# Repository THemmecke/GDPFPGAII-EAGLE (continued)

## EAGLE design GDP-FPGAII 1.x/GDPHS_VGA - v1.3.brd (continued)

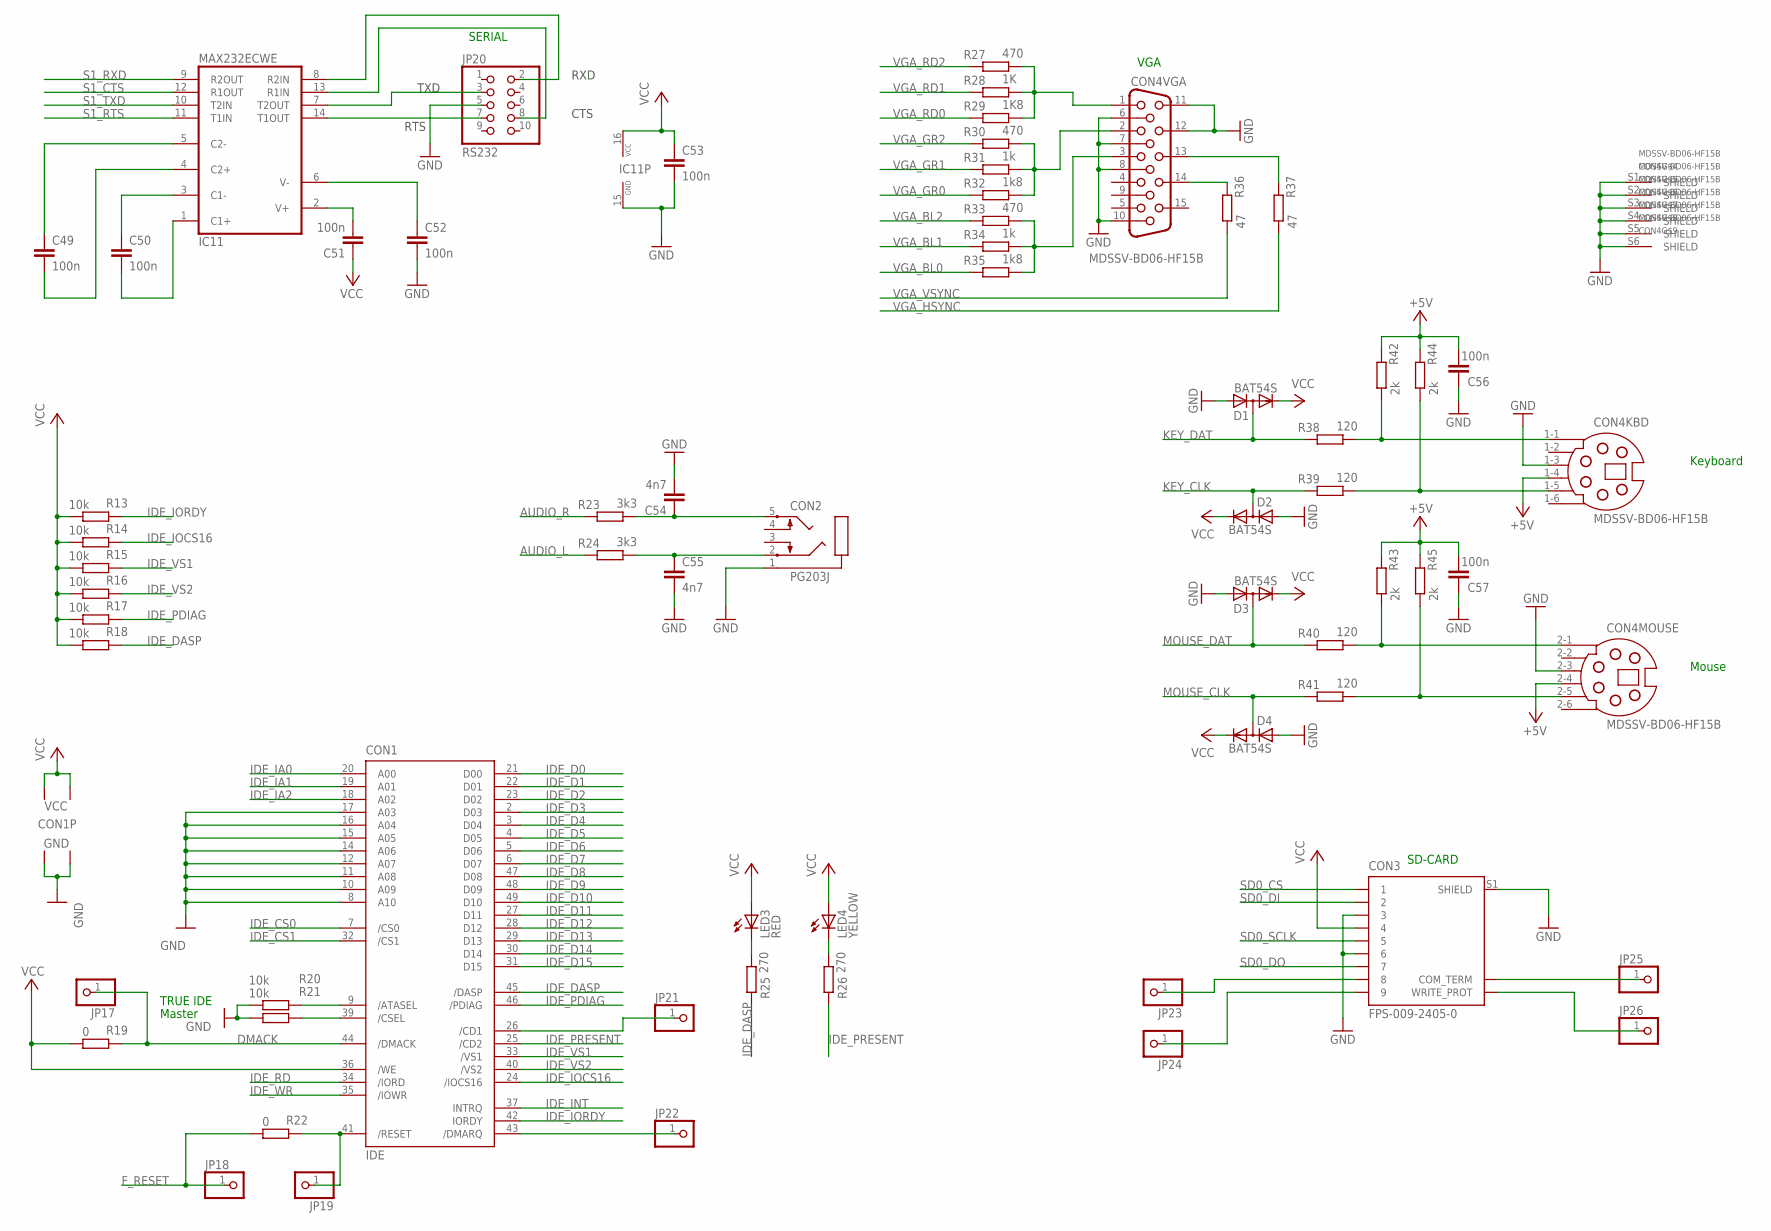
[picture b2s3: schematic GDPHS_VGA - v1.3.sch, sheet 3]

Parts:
C49, C50, C51, C52, C53, C56, C57: 100n; C0805
C54, C55: 4n7; C0805
CON1: IDE; CF-050-P2-X03-10-DS-1; MPN CF-050P2-103-10-DS1
CON2: PG203J
CON3: FPS-009-2405-0; MPN FPS-009-2405-0
CON4: MDSSV-BD06-HF15B; MDSSV-BD06-HF15-B; MPN 999-H15-PS2L571
D1, D2, D3, D4: BAT54S; SOT23
IC11: MAX232ECWE; SO16L
JP17, JP18, JP19, JP21, JP22, JP23, JP24, JP25, JP26: PINHD-1X1; 1X01
JP20: RS232; 2X05
LED3: RED; CHIPLED_0805
LED4: YELLOW; CHIPLED_0805
R13, R14, R15, R16, R17, R18, R20, R21: 10k; M0805
R19, R22: 0; M0805
R23, R24: 3k3; M0805
R25, R26: 270; M0805
R27, R30, R33: 470; M0805
R28: 1K; M0805
R29: 1K8; M0805
R31, R34: 1k; M0805
R32, R35: 1k8; M0805
R36, R37: 47; M0805
R38, R39, R40, R41: 120; M0805
R42, R43, R44, R45: 2k; M0805

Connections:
+5V: C56.2, C57.2, CON4.1-4 (4), CON4.2-4 (4), R42.1, R43.1, R44.1, R45.1; also elsewhere on the board
AUDIO_L: R24.1; also elsewhere on the board
AUDIO_R: R23.1; also elsewhere on the board
DMACK: CON1.44 (/DMACK), JP17.1, R19.1
F_RESET: JP18.1, R22.2; also elsewhere on the board
GND: C52.2, C53.2, C54.2, C55.2, C56.1, C57.1, CON1.1 (GND1), CON1.8 (A10), CON1.10 (A09), CON1.11 (A08), CON1.12 (A07), CON1.14 (A06), CON1.15 (A05), CON1.16 (A04), CON1.17 (A03), CON1.50 (GND2), CON2.1, CON3.3, CON3.6, CON3.S1 (SHIELD), CON4.1-3 (3), CON4.2-3 (3), CON4.6, CON4.7, CON4.8, CON4.10, CON4.11, CON4.12, CON4.S1 (SHIELD), CON4.S2 (SHIELD), CON4.S3 (SHIELD), CON4.S4 (SHIELD), CON4.S5 (SHIELD), CON4.S6 (SHIELD), D1.1 (A), D2.1 (A), D3.1 (A), D4.1 (A), IC11.15 (GND), JP20.5, R20.2, R21.2; also elsewhere on the board
IDE_CS0: CON1.7 (/CS0); also elsewhere on the board
IDE_CS1: CON1.32 (/CS1); also elsewhere on the board
IDE_D0: CON1.21 (D00); also elsewhere on the board
IDE_D1: CON1.22 (D01); also elsewhere on the board
IDE_D2: CON1.23 (D02); also elsewhere on the board
IDE_D3: CON1.2 (D03); also elsewhere on the board
IDE_D4: CON1.3 (D04); also elsewhere on the board
IDE_D5: CON1.4 (D05); also elsewhere on the board
IDE_D6: CON1.5 (D06); also elsewhere on the board
IDE_D7: CON1.6 (D07); also elsewhere on the board
IDE_D8: CON1.47 (D08); also elsewhere on the board
IDE_D9: CON1.48 (D09); also elsewhere on the board
IDE_D10: CON1.49 (D10); also elsewhere on the board
IDE_D11: CON1.27 (D11); also elsewhere on the board
IDE_D12: CON1.28 (D12); also elsewhere on the board
IDE_D13: CON1.29 (D13); also elsewhere on the board
IDE_D14: CON1.30 (D14); also elsewhere on the board
IDE_D15: CON1.31 (D15); also elsewhere on the board
IDE_DASP: CON1.45 (/DASP), R18.1, R25.1
IDE_IA0: CON1.20 (A00); also elsewhere on the board
IDE_IA1: CON1.19 (A01); also elsewhere on the board
IDE_IA2: CON1.18 (A02); also elsewhere on the board
IDE_INT: CON1.37 (INTRQ); also elsewhere on the board
IDE_IOCS16: CON1.24 (/IOCS16), R14.1
IDE_IORDY: CON1.42 (IORDY), R13.1
IDE_PDIAG: CON1.46 (/PDIAG), R17.1
IDE_PRESENT: CON1.25 (/CD2), R26.1
IDE_RD: CON1.34 (/IORD); also elsewhere on the board
IDE_VS1: CON1.33 (/VS1), R15.1
IDE_VS2: CON1.40 (/VS2), R16.1
IDE_WR: CON1.35 (/IOWR); also elsewhere on the board
KEY_CLK: D2.3 (AC), R39.1; also elsewhere on the board
KEY_DAT: D1.3 (AC), R38.1; also elsewhere on the board
MOUSE_CLK: D4.3 (AC), R41.1; also elsewhere on the board
MOUSE_DAT: D3.3 (AC), R40.1; also elsewhere on the board
unnamed: C50.2, IC11.1 (C1+)
unnamed: LED3.C, R25.2
unnamed: C50.1, IC11.3 (C1-)
unnamed: C49.2, IC11.4 (C2+)
unnamed: C49.1, IC11.5 (C2-)
unnamed: C52.1, IC11.6 (V-)
unnamed: C51.2, IC11.2 (V+)
unnamed: LED4.C, R26.2
unnamed: IC11.8 (R2IN), JP20.2
unnamed: IC11.13 (R1IN), JP20.8
unnamed: IC11.7 (T2OUT), JP20.3
unnamed: CON4.1, R27.2, R28.2, R29.2
unnamed: CON4.2, R30.2, R31.2, R32.2
unnamed: CON4.3, R33.2, R34.2, R35.2
unnamed: CON4.13, R37.1
unnamed: CON4.14, R36.1
unnamed: CON4.1-1 (1), R38.2, R42.2
unnamed: CON4.1-5 (5), R39.2, R44.2
unnamed: CON4.2-1 (1), R40.2, R43.2
unnamed: CON4.2-5 (5), R41.2, R45.2
unnamed: CON1.39 (/CSEL), R21.1
unnamed: CON1.9 (/ATASEL), R20.1
unnamed: C54.1, CON2.5, R23.2
unnamed: C55.1, CON2.2, R24.2
unnamed: IC11.14 (T1OUT), JP20.7
unnamed: CON1.41 (/RESET), JP19.1, R22.1
unnamed: CON1.43 (/DMARQ), JP22.1
unnamed: CON1.26 (/CD1), JP21.1
unnamed: CON3.8, JP23.1
unnamed: CON3.9, JP24.1
unnamed: CON3.CD (COM_TERM), JP25.1
unnamed: CON3.WP (WRITE_PROT), JP26.1
S1_CTS: IC11.12 (R1OUT); also elsewhere on the board
S1_RTS: IC11.11 (T1IN); also elsewhere on the board
S1_RXD: IC11.9 (R2OUT); also elsewhere on the board
S1_TXD: IC11.10 (T2IN); also elsewhere on the board
SD0_CS: CON3.1; also elsewhere on the board
SD0_DI: CON3.2; also elsewhere on the board
SD0_DO: CON3.7; also elsewhere on the board
SD0_SCLK: CON3.5; also elsewhere on the board
VCC: C51.1, C53.1, CON1.13 (VCC2), CON1.36 (/WE), CON1.38 (VCC1), CON3.4, D1.2 (C), D2.2 (C), D3.2 (C), D4.2 (C), IC11.16 (VCC), LED3.A, LED4.A, R13.2, R14.2, R15.2, R16.2, R17.2, R18.2, R19.2; also elsewhere on the board
VGA_BL0: R35.1; also elsewhere on the board
VGA_BL1: R34.1; also elsewhere on the board
VGA_BL2: R33.1; also elsewhere on the board
VGA_GR0: R32.1; also elsewhere on the board
VGA_GR1: R31.1; also elsewhere on the board
VGA_GR2: R30.1; also elsewhere on the board
VGA_HSYNC: R37.2; also elsewhere on the board
VGA_RD0: R29.1; also elsewhere on the board
VGA_RD1: R28.1; also elsewhere on the board
VGA_RD2: R27.1; also elsewhere on the board
VGA_VSYNC: R36.2; also elsewhere on the board

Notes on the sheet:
SERIAL
SD-CARD
VGA
Keyboard
Mouse
Master
TRUE IDE
RXD
CTS
TXD
RTS

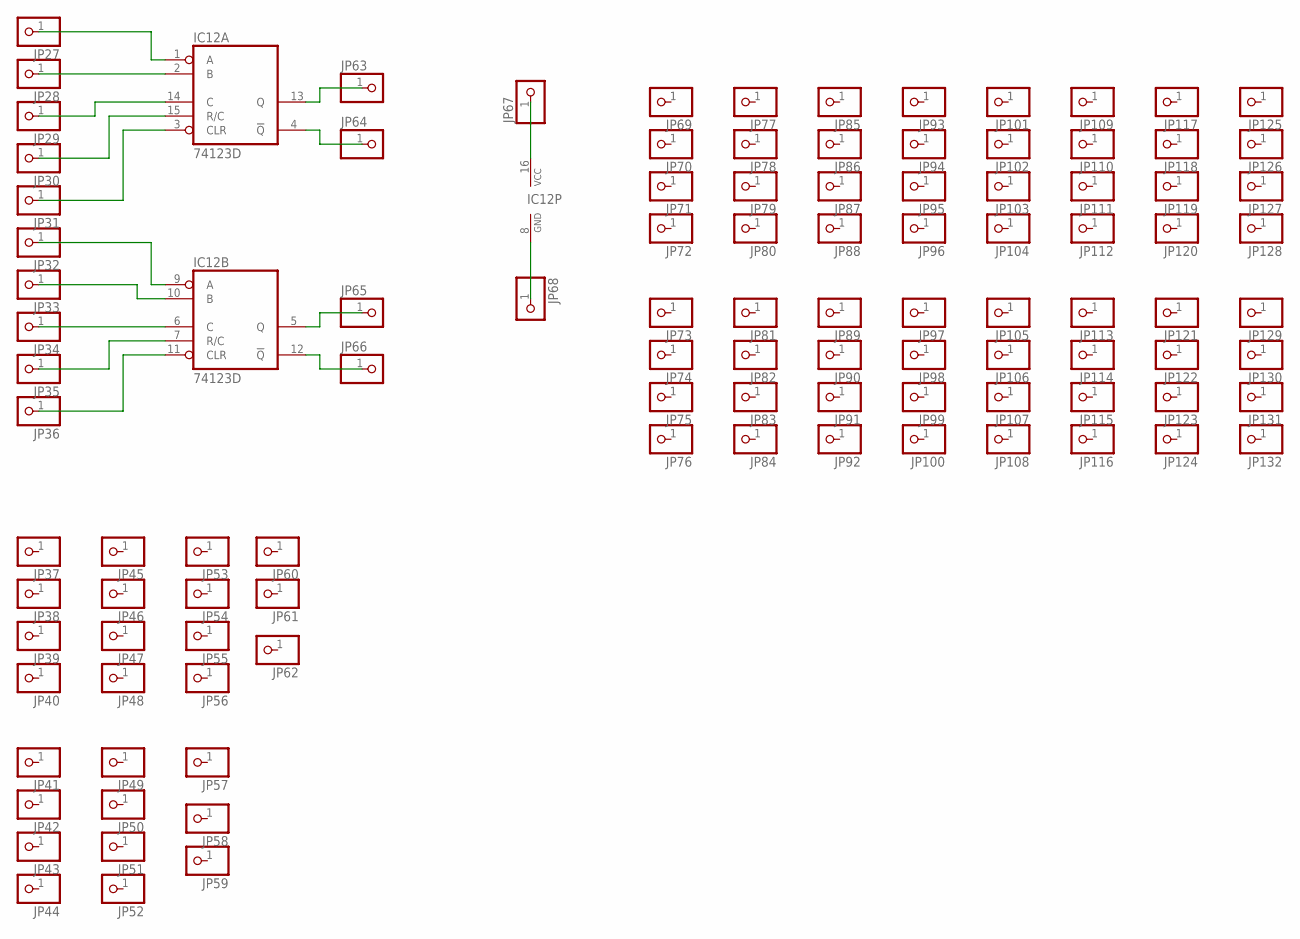
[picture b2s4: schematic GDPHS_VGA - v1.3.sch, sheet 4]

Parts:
IC12: 74123D; SO16
JP27, JP28, JP29, JP30, JP31, JP32, JP33, JP34, JP35, JP36, JP37, JP38, JP39, JP40, JP41, JP42, JP43, JP44, JP45, JP46, JP47, JP48, JP49, JP50, JP51, JP52, JP53, JP54, JP55, JP56, JP57, JP58, JP59, JP60, JP61, JP62, JP63, JP64, JP65, JP66, JP67, JP68, JP69, JP70, JP71, JP72, JP73, JP74, JP75, JP76, JP77, JP78, JP79, JP80, JP81, JP82, JP83, JP84, JP85, JP86, JP87, JP88, JP89, JP90, JP91, JP92, JP93, JP94, JP95, JP96, JP97, JP98, JP99, JP100, JP101, JP102, JP103, JP104, JP105, JP106, JP107, JP108, JP109, JP110, JP111, JP112, JP113, JP114, JP115, JP116, JP117, JP118, JP119, JP120, JP121, JP122, JP123, JP124, JP125, JP126, JP127, JP128, JP129, JP130, JP131, JP132: PINHD-1X1; 1X01

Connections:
unnamed: IC12.1 (A), JP27.1
unnamed: IC12.2 (B), JP28.1
unnamed: IC12.14 (C), JP29.1
unnamed: IC12.15 (R/C), JP30.1
unnamed: IC12.3 (CLR), JP31.1
unnamed: IC12.13 (Q), JP63.1
unnamed: IC12.4 (!Q), JP64.1
unnamed: IC12.9 (A), JP32.1
unnamed: IC12.10 (B), JP33.1
unnamed: IC12.6 (C), JP34.1
unnamed: IC12.16 (VCC), JP67.1
unnamed: IC12.8 (GND), JP68.1
unnamed: IC12.7 (R/C), JP35.1
unnamed: IC12.11 (CLR), JP36.1
unnamed: IC12.5 (Q), JP65.1
unnamed: IC12.12 (!Q), JP66.1

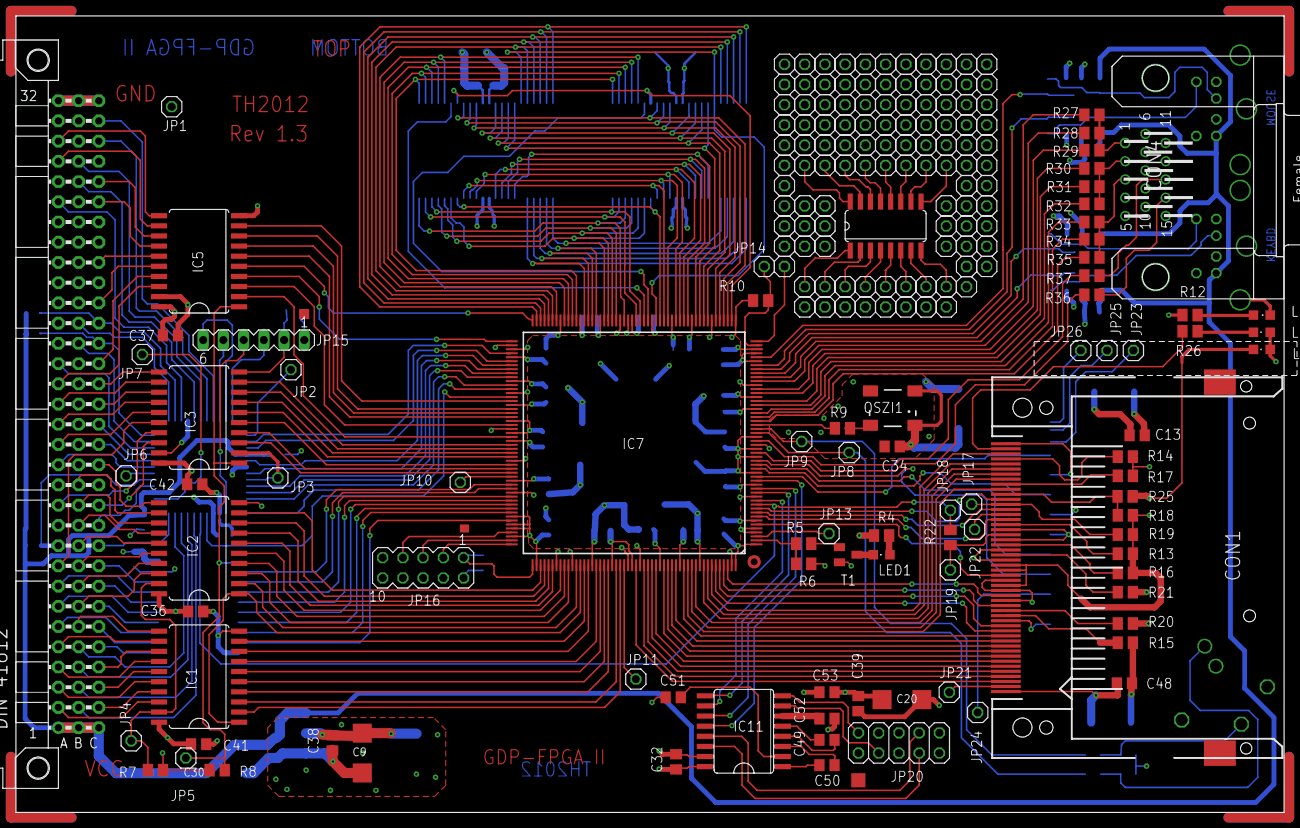
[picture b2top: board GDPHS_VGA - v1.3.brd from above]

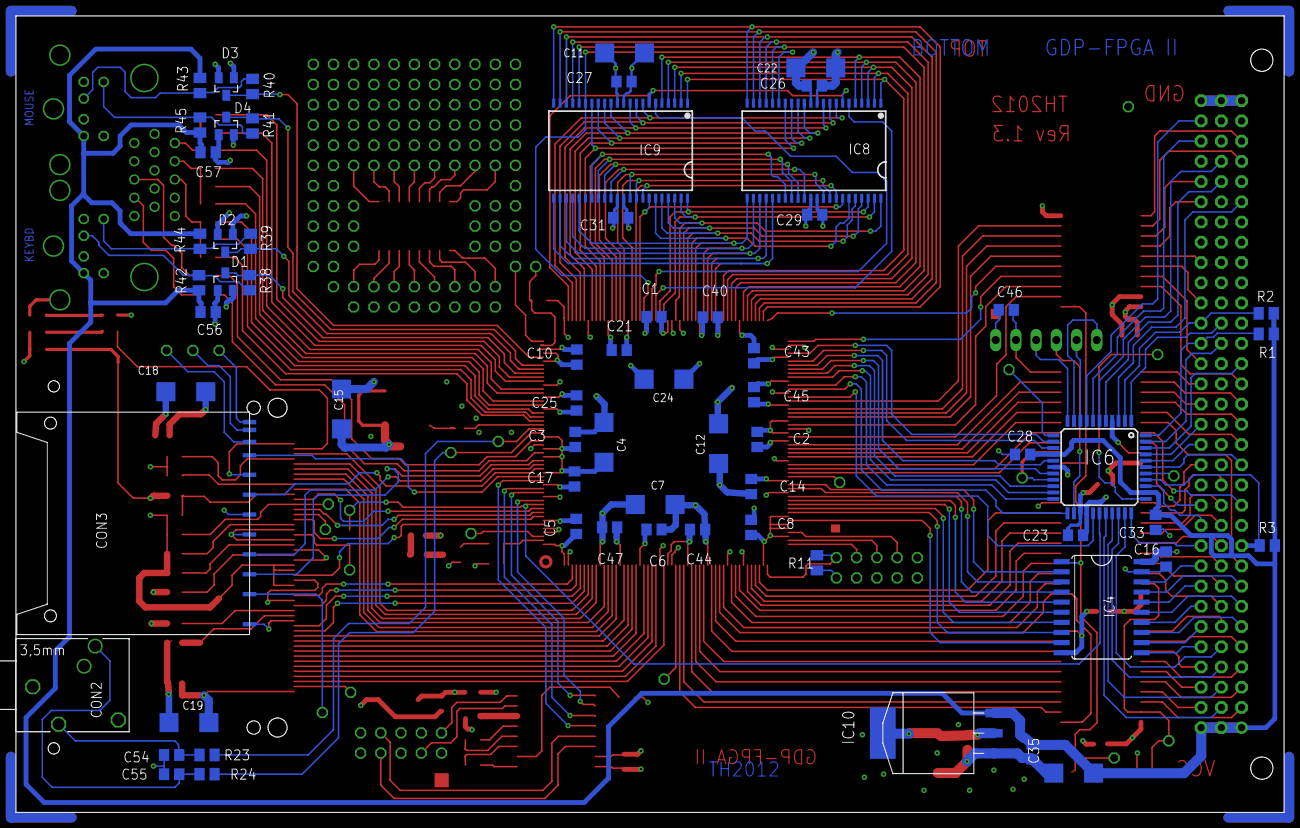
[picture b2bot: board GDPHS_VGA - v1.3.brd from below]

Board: 4 copper layers, 159.3 x 100.0 mm, 261 parts (65 on the bottom side), 284 nets.

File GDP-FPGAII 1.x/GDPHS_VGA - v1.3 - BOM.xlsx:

Qty | Value | Device | Package | Parts | Description | MF | MPN | DIGIKEY | FARNELL | REICHELT
4 | 0 | R-EU_M0805 | M0805 | R7, R8, R19, R22 | RESISTOR, European symbol |  |  |  |  | SMD-0805 [10,0K]
1 | 100 | R-EU_M0805 | M0805 | R10 | RESISTOR, European symbol |  |  |  |  | SMD-0805 [10,0K]
43 | 100n | C-EUC0805 | C0805 | C1, C2, C3, C5, C6, C8, C10, C13, C14, C16, C17, C21, C23, C25, C26, C27, C28, 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 | CAPACITOR, European symbol |  |  |  |  | X7R-G0805 [100N]
12 | 10k | R-EU_M0805 | M0805 | R1, R2, R3, R6, R13, R14, R15, R16, R17, R18, R20, R21 | RESISTOR, European symbol |  |  |  |  | SMD-0805 [10,0K]
12 | 10µ/16 | CPOL-EUSMCC | SMC_C | C4, C7, C9, C11, C12, C15, C18, C19, C20, C22, C24, C30 | POLARIZED CAPACITOR, European symbol |  |  |  |  | SMD TAN [10/16]
4 | 120 | R-EU_M0805 | M0805 | R38, R39, R40, R41 | RESISTOR, European symbol |  |  |  |  | SMD-0805 [10,0K]
1 | 1K | R-EU_M0805 | M0805 | R28 | RESISTOR, European symbol |  |  |  |  | SMD-0805 [10,0K]
1 | 1K8 | R-EU_M0805 | M0805 | R29 | RESISTOR, European symbol |  |  |  |  | SMD-0805 [10,0K]
2 | 1k | R-EU_M0805 | M0805 | R31, R34 | RESISTOR, European symbol |  |  |  |  | SMD-0805 [10,0K]
2 | 1k8 | R-EU_M0805 | M0805 | R32, R35 | RESISTOR, European symbol |  |  |  |  | SMD-0805 [10,0K]
1 | 220 | R-EU_M0805 | M0805 | R4 | RESISTOR, European symbol |  |  |  |  | SMD-0805 [10,0K]
3 | 270 | R-EU_M0805 | M0805 | R12, R25, R26 | RESISTOR, European symbol |  |  |  |  | SMD-0805 [10,0K]
4 | 2k | R-EU_M0805 | M0805 | R42, R43, R44, R45 | RESISTOR, European symbol |  |  |  |  | SMD-0805 [10,0K]
1 | 330 | R-EU_M0805 | M0805 | R9 | RESISTOR, European symbol |  |  |  |  | SMD-0805 [10,0K]
2 | 3k3 | R-EU_M0805 | M0805 | R23, R24 | RESISTOR, European symbol |  |  |  |  | SMD-0805 [10,0K]
2 | 47 | R-EU_M0805 | M0805 | R36, R37 | RESISTOR, European symbol |  |  |  |  | SMD-0805 [10,0K]
3 | 470 | R-EU_M0805 | M0805 | R27, R30, R33 | RESISTOR, European symbol |  |  |  |  | SMD-0805 [10,0K]
1 | 4k7 | R-EU_M0805 | M0805 | R11 | RESISTOR, European symbol |  |  |  |  | SMD-0805 [10,0K]
2 | 4n7 | C-EUC0805 | C0805 | C54, C55 | CAPACITOR, European symbol |  |  |  |  | X7R-G0805 [100N]
1 | 5k6 | R-EU_M0805 | M0805 | R5 | RESISTOR, European symbol |  |  |  |  | SMD-0805 [10,0K]
1 | 74123D | 74123D | SO16 | IC12 | Retriggerable monostable MULTIVIBRATOR
5 | 74LVC245 | 74HCT245DW | SO20W | IC1, IC2, IC3, IC4, IC5 | Octal BUS TRANSCEIVER, 3-state | Texas Instruments | SN74LVC245ADWR | 296-1232-1-ND
4 | BAT54S | DIODE_2CACA-SOT23 | SOT23 | D1, D2, D3, D4 | 2 Diodes - Cathode-Anode|Cathode-Anode |  |  |  |  | BAT 54S SMD
1 | BSS138 | BSS123 | SOT23 | T1 | N-CHANNEL MOS FET | Fairchild Semiconductor | BSS138 |  |  | BSS 138 SMD
1 | CFPS-39 40MHz | CRYSTAL_RESONATORCFPS7X | CFPS7X | OSZI1 | CRYSTAL RESONATOR | IQD FREQUENCY PRODUCTS | LF SPXO018042 - QUARZ, 40MHZ, 15PF, SMD |  | 9713565
2 | CY7C1041CV33-TSOP44 | CY7C1041CV33-TSOP44 | TSOP44-400 | IC8, IC9 |  | Cypress | CY7C1041CV33-10ZSXA | CY7C1041CV33-10ZSXA-ND
1 | ECB-BUS | VG96K | VG96K | J1 | PCB EUROCARD, 96-pin type C/ABC, 2.54 mm |  |  |  |  | ML-C 96W
1 | FPS-009-2405-0 | FPS-009-2405-0 | FPS-009-2405-0 | CON3 | YAMAI SD Card - FPS Series 009-2405-0 | Yamaichi | FPS-009-2405-0 |  |  | CONNECTOR SD 22
1 | GREEN | LEDCHIPLED_0805 | CHIPLED_0805 | LED2 | LED |  |  |  |  | SMD-LED 1206 GN
1 | IDE | CF-CARD-IDE_MODEYAMAI-CF-CARD-I-II | CF-050-P2-X03-10-DS-1 | CON1 | Compact Flash Adapter Type I or II without Eject Button | Yamaichi | CF-050P2-103-10-DS1 |  |  | CONNECTOR CF 02
1 | LFXP6C_XX208-2 | LFXP6C_XX208-2 | PQFP_208 | IC7 |  | Lattice Semiconductor | LFXP6C-3QN208C | 220-1261-ND
1 | LT1086-3.3V | LT1086 | MDD | IC10 |  | Linear Technology | LT1086CM-3.3#PBF | LT1086CM-3.3#PBF-ND
1 | LatticeProg | MA05-2 | MA05-2 | JP16 | PIN HEADER |  |  |  | unknown
1 | MAX232ECWE | MAX232ECWE | SO16L | IC11 | RS232 TRANSEIVER | MAXIM | MAX232ECWE+ |  | 9724435
1 | MDSSV-BD06-HF15B | MDSSV-BD06-HF15B | MDSSV-BD06-HF15-B | CON4 |  | Norcomp Inc. | 999-H15-PS2L571 | 999-H15FA-ND
1 | PG203J | PG203J | PG203J | CON2 | MIC/HEADPHONE JACK |  |  |  | unknown | EBS 35 BL
1 | RED | LEDCHIPLED_0805 | CHIPLED_0805 | LED3 | LED |  |  |  |  | SMD-LED 1206 RT
1 | RS232 | PINHD-2X5 | 2X05 | JP20 | PIN HEADER
1 | XC9536SMD | XC9536SMD | TQFP44 | IC6 |  | Xilinx | XC9536-7VQ44C | 122-1170-ND
1 | XilinxProg | MA06-1 | MA06-1 | JP15 | PIN HEADER |  |  |  | unknown
2 | YELLOW | LEDCHIPLED_0805 | CHIPLED_0805 | LED1, LED4 | LED |  |  |  |  | SMD-LED 1206 GE

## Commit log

2015-09-04 added GDPHS_VGA - v2.2.1.sch
2021-07-22 Doc fixes
